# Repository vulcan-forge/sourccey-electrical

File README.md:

# Sourccey Electrical

Open-source hardware design files for the Sourccey electrical system.

This repository is intended to contain the complete KiCad design source,
component data, and documentation needed to inspect, modify, manufacture,
and assemble the hardware.

## Status

This repository contains the Sourccey v1.3.8 electrical design release.
Always review the release notes and complete your own manufacturing and safety
validation before building hardware.

## Repository layout

The repository is organized by editable design sources, manufacturing outputs,
and supporting documentation:

```text
.
├── pcb/
│   ├── <board-name>.kicad_pro
│   ├── <board-name>.kicad_sch
│   ├── <board-name>.kicad_pcb
│   ├── symbols/             # Project-specific KiCad symbols
│   └── footprints/          # Project-specific KiCad footprints
├── bom/
│   ├── bom.csv              # Human/reviewable bill of materials
│   └── pos.csv              # Pick-and-place / centroid data
├── fab/                     # Released Gerbers and drill files, if tracked
├── docs/                    # Design notes, assembly, and test instructions
└── README.md
```

The generic layout above describes the intended convention for additional
boards. The current checked-in release is organized as follows:

```text
.
|-- pcb/sourccey-v1.3.8/
|   |-- *.kicad_pro       # KiCad project
|   |-- *.kicad_sch       # Main and hierarchical schematics
|   |-- *.kicad_pcb       # PCB layout
|   |-- symbols/           # Project-specific KiCad symbols
|   |-- footprints/        # Project-specific KiCad footprints
|   `-- models/            # Optional 3D model references
|-- manufacturing/sourccey-v1.3.8/
|   |-- gerbers/           # Gerbers, drill files, and Gerber archive
|   |-- bom/               # Bill of materials exports
|   `-- cpl/               # Pick-and-place / component placement exports
|-- docs/                  # Design notes, assembly, and test instructions
`-- README.md
```

Each board should keep its `.kicad_pro`,
`.kicad_sch`, and `.kicad_pcb` files together. Do not commit KiCad lock files,
personal project settings, or backup files.

## Opening the design

The current design is Sourccey v1.3.8 and was saved with KiCad 9.0.

1. Install [KiCad 9](https://www.kicad.org/download/), including the standard
   symbol, footprint, and 3D-model libraries.
2. Clone this repository.
3. Open
   `pcb/sourccey-v1.3.8/sourccey_pcb.kicad_pro`.
4. Review the schematic before opening or editing the PCB.
5. Update the project libraries only with care: project-local symbols and
   footprints should be stored in this repository so the design remains
   reproducible.

The project includes its hierarchical `Power Electronics.kicad_sch` sheet and
the custom DRV8874 symbol and footprint. See the README under the version's
`models/` directory for two optional STEP models that are not yet included.

## BOM and POS data

The `manufacturing/sourccey-v1.3.8/` directory contains the files needed to
order and assemble the board:

- Gerbers for copper, solder mask, solder paste, silkscreen, and the board
  outline, plus the Gerber job file and packaged archive.
- PTH and NPTH drill files for plated and non-plated holes.
- A KiCad BOM export and a vendor-formatted BOM for purchasing.
- KiCad and vendor-formatted CPL (component placement / pick-and-place) data.

These are manufacturing outputs, not the editable source of truth. Regenerate
them from the released KiCad project whenever the design changes.

The BOM should identify at least:

- Reference designators
- Quantity
- Value and footprint
- Manufacturer and manufacturer part number, when known
- Distributor part number, when known
- Designator exclusions or DNP status

The POS file should identify each populated reference, X/Y position, rotation,
side, and the coordinate origin used for the export. BOM and POS exports are
manufacturing inputs: regenerate them from the released KiCad sources and
record the KiCad version and export settings in the release notes.

## Manufacturing components

Manufacturing outputs are generated from the released PCB source. A release
should include, or link to, the corresponding Gerber, drill, drawing, BOM, and
POS package. Keep generated outputs in `fab/` or a release artifact rather than
mixing them with editable KiCad source files.

The checked-in v1.3.8 outputs are under
`manufacturing/sourccey-v1.3.8/`, including original and vendor-formatted BOM
and CPL files, Gerbers, drill files, and the Gerber archive.

The PCB uses 2 oz copper on the copper layers. Confirm the fabricator's stackup
and copper-weight capabilities before ordering.

Before manufacturing, check at minimum:

- Schematic and PCB annotations are synchronized.
- Electrical rules and design rules pass.
- Board outline, mounting holes, clearances, and layer stack are correct.
- Footprints and 3D/component orientations are correct.
- BOM substitutions, DNP parts, polarity, and assembly side are reviewed.
- Gerbers and drill files are inspected in a separate viewer.

## Documentation

See the [Vulcan Robotics documentation](https://vulcanrobotics.ai/docs) for the
broader Sourccey project. This repository is the electrical reference for
wiring and board-level build details. The documentation site also links to the
related hardware, software, and LeRobot-compatible repositories. Software setup
and hardware-kit assembly instructions are currently listed there as coming
soon.

## Release notes

See [RELEASE_NOTES.md](RELEASE_NOTES.md) for the v1.3.8 release summary,
manufacturing package details, and validation record.

## Contributing

Please open an issue before making a substantial design change. Pull requests
should explain the motivation, identify affected boards, and include updated
schematic/PCB files and regenerated BOM/POS or manufacturing outputs when
applicable. Include screenshots or test results for changes that affect layout,
assembly, or electrical behavior.

## Licensing

Unless stated otherwise in a subdirectory, this project is released under the
[CERN Open Hardware Licence Version 2 - Strongly Reciprocal
(CERN-OHL-S-2.0)](https://gitlab.com/ohwr/project/cernohl/-/wikis/uploads/819d71bea3458f71fba6cf4fb0f2de6b/cern_ohl_s_v2.txt).
This license permits personal, educational, commercial, and manufacturing use.
If you distribute a modified design or a product based on it, you must preserve
the notices, make the corresponding source available, and license the modified
covered source under CERN-OHL-S-2.0. Private modifications do not need to be
published unless they are distributed.

Add the full license text as `LICENSE` before publishing the repository.

Third-party symbols, footprints, models, and datasheets may have separate
licenses. Preserve their notices and verify redistribution rights before
committing them.

## Disclaimer

This hardware is provided without warranty. You are responsible for reviewing
the design, complying with applicable laws and safety requirements, and
validating any manufactured or modified hardware before use.

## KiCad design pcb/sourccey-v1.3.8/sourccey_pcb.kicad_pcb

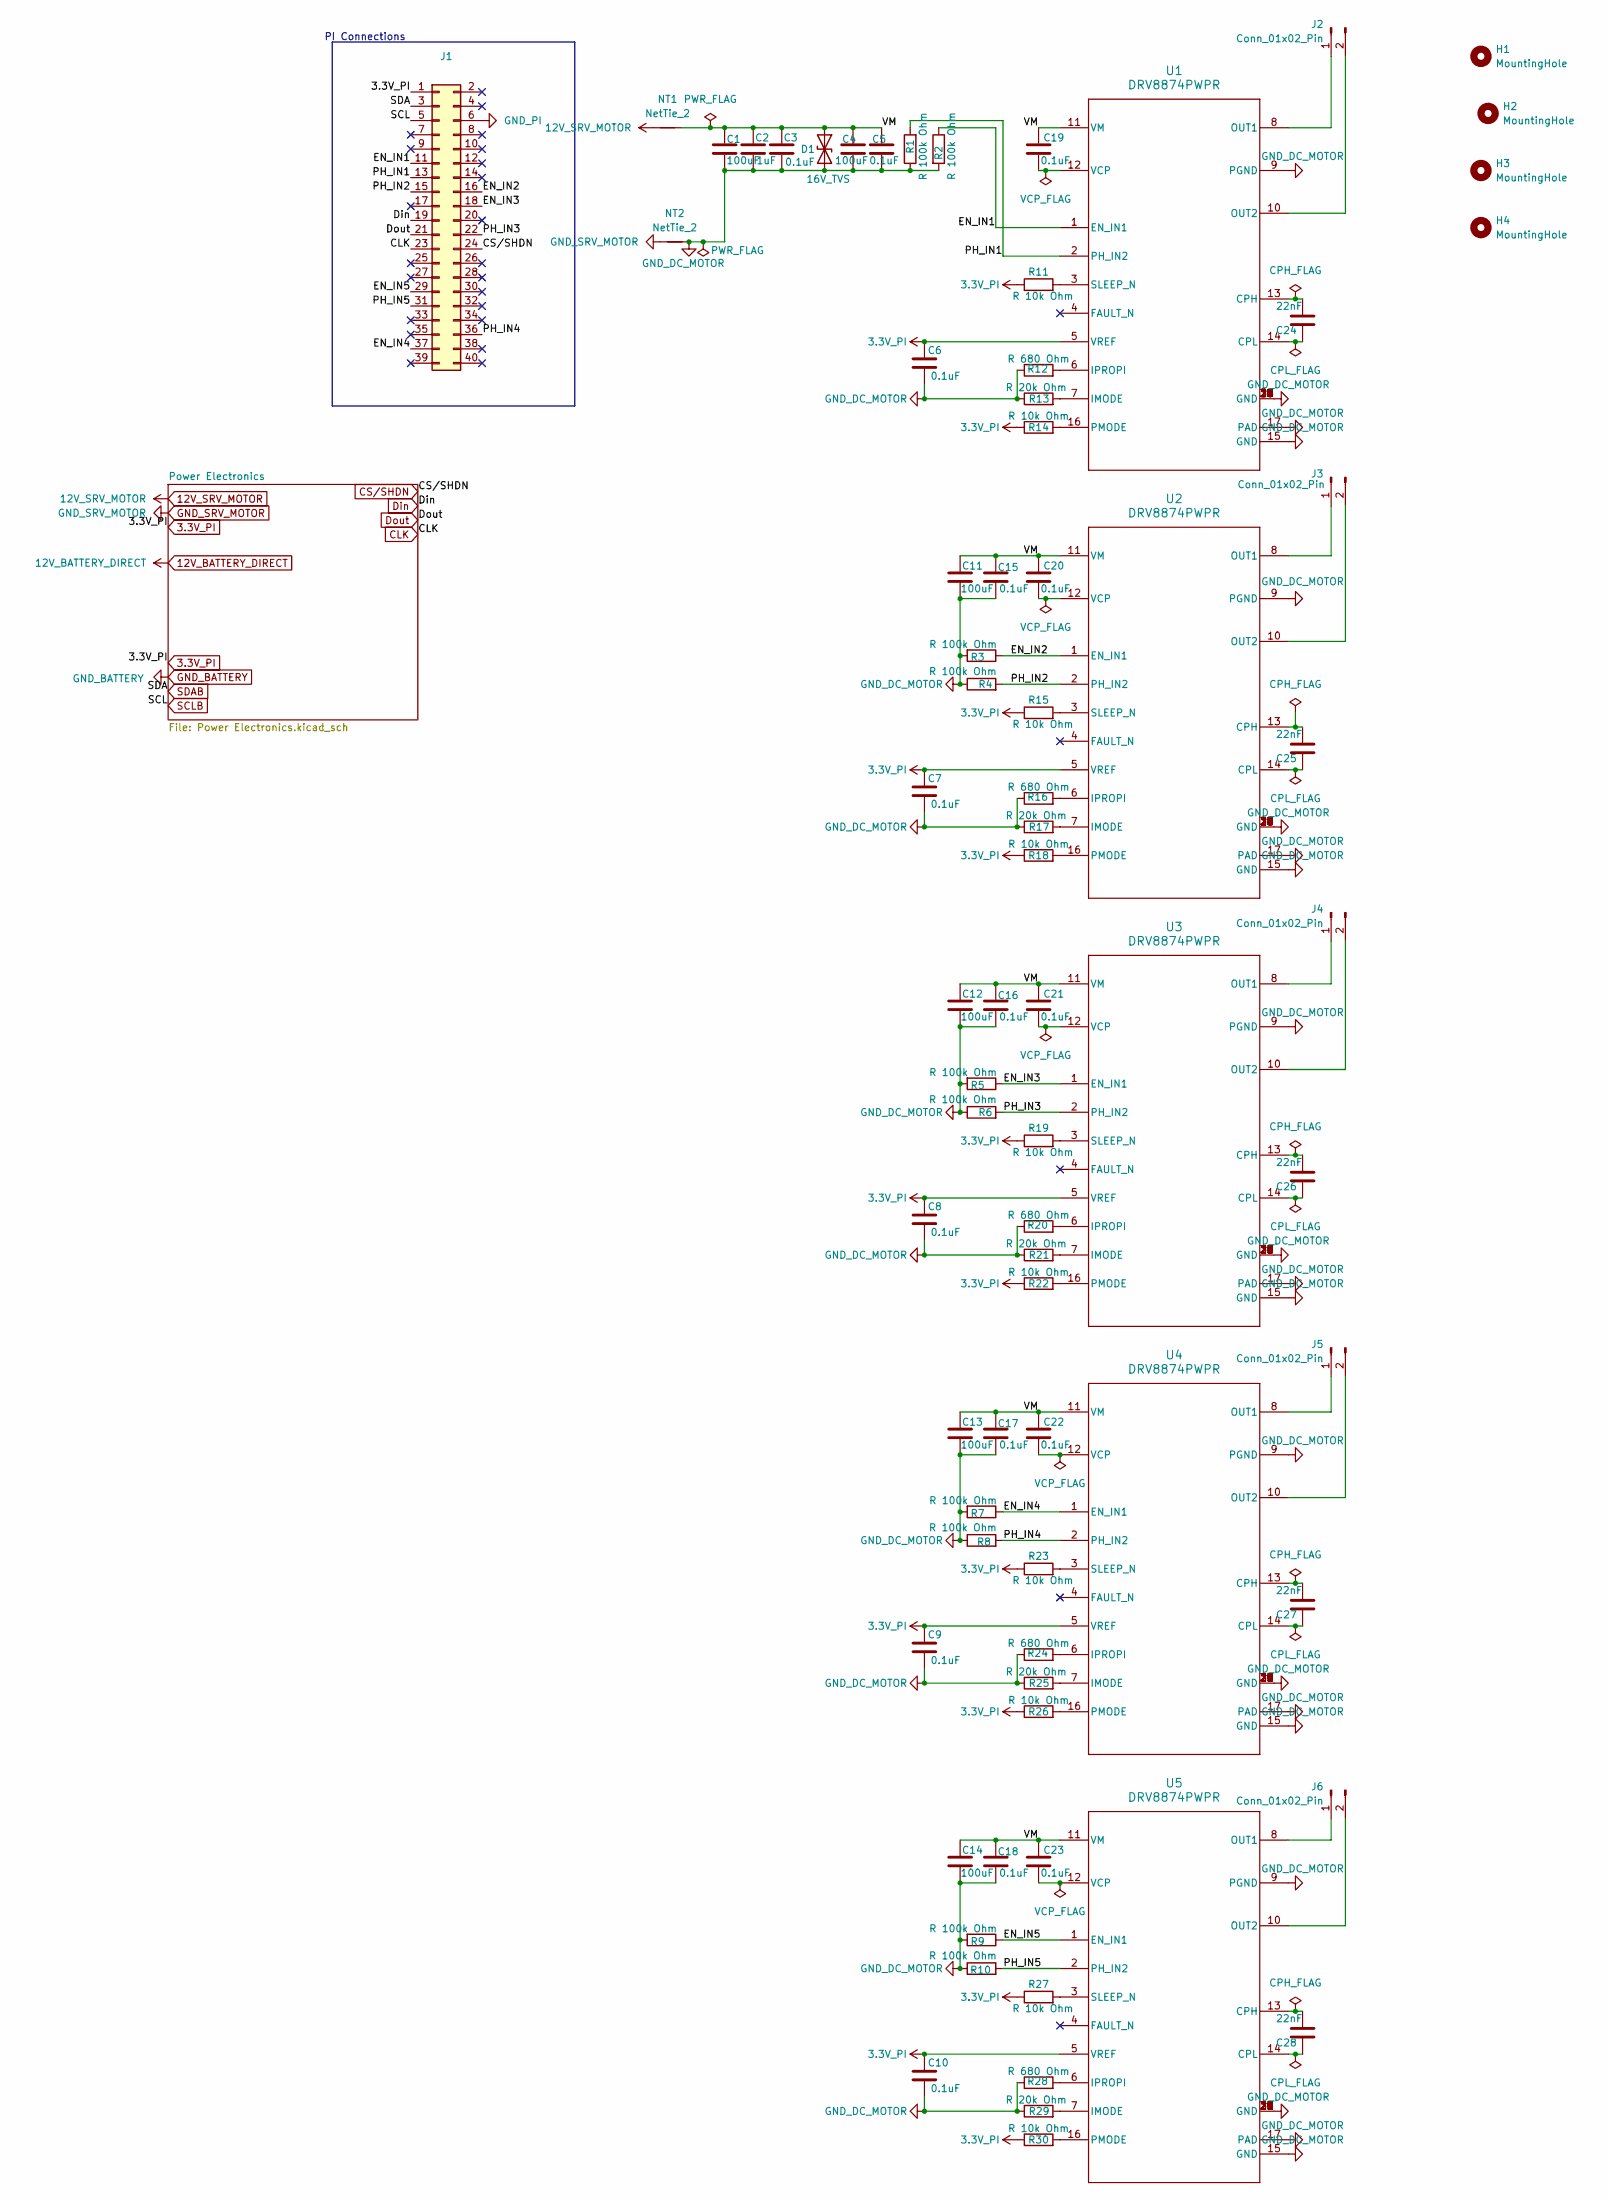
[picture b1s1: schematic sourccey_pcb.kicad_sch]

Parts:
C1, C4, C11, C12, C13, C14: 100uF; CP_Elec_6.3x7.7
C2: 1uF; C_0805_2012Metric
C3, C5, C6, C7, C8, C9, C10, C15, C16, C17, C18, C19, C20, C21, C22, C23: 0.1uF; C_0603_1608Metric
C24, C25, C26, C27, C28: 22nF; C_0402_1005Metric
D1: 16V_TVS; D_SMB
H1, H2, H3, H4: MountingHole; MountingHole_3.2mm_M3
J1: Conn_02x20_Odd_Even; PinHeader_2x20_P2.54mm_Vertical
J2, J3, J4, J5, J6: Conn_01x02_Pin; AMASS_XT30UPB-M_1x02_P5.0mm_Vertical
NT1, NT2: NetTie_2; NetTie-2_SMD_Pad2.0mm
R1, R2, R3, R4, R5, R6, R7, R8, R9, R10: R 100k Ohm; R_0805_2012Metric
R11, R14, R15, R18, R19, R22, R23, R26, R27, R30: R 10k Ohm; R_0805_2012Metric
R12, R16, R20, R24, R28: R 680 Ohm; R_0805_2012Metric
R13, R17, R21, R25, R29: R 20k Ohm; R_0805_2012Metric
U1, U2, U3, U4, U5: DRV8874PWPR; PWP0016J_L

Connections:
3.3V_PI: C6.2, C7.2, C8.2, C9.2, C10.2, J1.1, R11.1, R14.1, R15.1, R18.1, R19.1, R22.1, R23.1, R26.1, R27.1, R30.1, U1.5 (VREF), U2.5 (VREF), U3.5 (VREF), U4.5 (VREF), U5.5 (VREF); also elsewhere on the board
12V_SRV_MOTOR: NT1.1; also elsewhere on the board
/EN_IN1: J1.11, R2.1, U1.1 (EN_IN1)
/EN_IN2: J1.16, R3.1, U2.1 (EN_IN1)
/EN_IN3: J1.18, R5.1, U3.1 (EN_IN1)
/EN_IN4: J1.37, R7.1, U4.1 (EN_IN1)
/EN_IN5: J1.29, R9.1, U5.1 (EN_IN1)
/PH_IN1: J1.13, R1.2, U1.2 (PH_IN2)
/PH_IN2: J1.15, R4.2, U2.2 (PH_IN2)
/PH_IN3: J1.22, R6.2, U3.2 (PH_IN2)
/PH_IN4: J1.36, R8.2, U4.2 (PH_IN2)
/PH_IN5: J1.31, R10.2, U5.2 (PH_IN2)
/VM: C1.1, C2.1, C3.1, C4.1, C5.1, C11.1, C12.1, C13.1, C14.1, C15.1, C16.1, C17.1, C18.1, C19.1, C20.1, C21.1, C22.1, C23.1, D1.1 (A1), NT1.2, U1.11 (VM), U2.11 (VM), U3.11 (VM), U4.11 (VM), U5.11 (VM)
CLK: J1.23; also elsewhere on the board
CS/SHDN: J1.24; also elsewhere on the board
Din: J1.19; also elsewhere on the board
Dout: J1.21; also elsewhere on the board
GND_DC_MOTOR: C1.2, C2.2, C3.2, C4.2, C5.2, C6.1, C7.1, C8.1, C9.1, C10.1, C11.2, C12.2, C13.2, C14.2, C15.2, C16.2, C17.2, C18.2, D1.2 (A2), NT2.2, R1.1, R2.2, R3.2, R4.1, R5.2, R6.1, R7.2, R8.1, R9.2, R10.1, R12.1, R13.1, R16.1, R17.1, R20.1, R21.1, R24.1, R25.1, R28.1, R29.1, U1.9 (PGND), U1.15 (GND), U1.17 (PAD), U1.18 (GND), U1.19 (GND), U1.20 (GND), U1.21 (GND), U1.22 (GND), U1.23 (GND), U1.24 (GND), U1.25 (GND), U1.26 (GND), U1.27 (GND), U1.28 (GND), U1.29 (GND), U1.30 (GND), U1.31 (GND), U1.32 (GND), U2.9 (PGND), U2.15 (GND), U2.17 (PAD), U2.18 (GND), U2.19 (GND), U2.20 (GND), U2.21 (GND), U2.22 (GND), U2.23 (GND), U2.24 (GND), U2.25 (GND), U2.26 (GND), U2.27 (GND), U2.28 (GND), U2.29 (GND), U2.30 (GND), U2.31 (GND), U2.32 (GND), U3.9 (PGND), U3.15 (GND), U3.17 (PAD), U3.18 (GND), U3.19 (GND), U3.20 (GND), U3.21 (GND), U3.22 (GND), U3.23 (GND), U3.24 (GND), U3.25 (GND), U3.26 (GND), U3.27 (GND), U3.28 (GND), U3.29 (GND), U3.30 (GND), U3.31 (GND), U3.32 (GND), U4.9 (PGND), U4.15 (GND), U4.17 (PAD), U4.18 (GND), U4.19 (GND), U4.20 (GND), U4.21 (GND), U4.22 (GND), U4.23 (GND), U4.24 (GND), U4.25 (GND), U4.26 (GND), U4.27 (GND), U4.28 (GND), U4.29 (GND), U4.30 (GND), U4.31 (GND), U4.32 (GND), U5.9 (PGND), U5.15 (GND), U5.17 (PAD), U5.18 (GND), U5.19 (GND), U5.20 (GND), U5.21 (GND), U5.22 (GND), U5.23 (GND), U5.24 (GND), U5.25 (GND), U5.26 (GND), U5.27 (GND), U5.28 (GND), U5.29 (GND), U5.30 (GND), U5.31 (GND), U5.32 (GND); also elsewhere on the board
GND_PI: J1.6; also elsewhere on the board
GND_SRV_MOTOR: NT2.1; also elsewhere on the board
unnamed: J2.1, U1.8 (OUT1)
unnamed: J2.2, U1.10 (OUT2)
unnamed: J3.1, U2.8 (OUT1)
unnamed: J3.2, U2.10 (OUT2)
unnamed: J4.1, U3.8 (OUT1)
unnamed: J4.2, U3.10 (OUT2)
unnamed: J5.1, U4.8 (OUT1)
unnamed: J5.2, U4.10 (OUT2)
unnamed: J6.1, U5.8 (OUT1)
unnamed: J6.2, U5.10 (OUT2)
unnamed: C24.1, U1.13 (CPH)
unnamed: C24.2, U1.14 (CPL)
unnamed: R13.2, U1.7 (IMODE)
unnamed: R12.2, U1.6 (IPROPI)
unnamed: R14.2, U1.16 (PMODE)
unnamed: R11.2, U1.3 (SLEEP_N)
unnamed: C19.2, U1.12 (VCP)
unnamed: C25.1, U2.13 (CPH)
unnamed: C25.2, U2.14 (CPL)
unnamed: R17.2, U2.7 (IMODE)
unnamed: R16.2, U2.6 (IPROPI)
unnamed: R18.2, U2.16 (PMODE)
unnamed: R15.2, U2.3 (SLEEP_N)
unnamed: C20.2, U2.12 (VCP)
unnamed: C26.1, U3.13 (CPH)
unnamed: C26.2, U3.14 (CPL)
unnamed: R21.2, U3.7 (IMODE)
unnamed: R20.2, U3.6 (IPROPI)
unnamed: R22.2, U3.16 (PMODE)
unnamed: R19.2, U3.3 (SLEEP_N)
unnamed: C21.2, U3.12 (VCP)
unnamed: C27.1, U4.13 (CPH)
unnamed: C27.2, U4.14 (CPL)
unnamed: R25.2, U4.7 (IMODE)
unnamed: R24.2, U4.6 (IPROPI)
unnamed: R26.2, U4.16 (PMODE)
unnamed: R23.2, U4.3 (SLEEP_N)
unnamed: C22.2, U4.12 (VCP)
unnamed: C28.1, U5.13 (CPH)
unnamed: C28.2, U5.14 (CPL)
unnamed: R29.2, U5.7 (IMODE)
unnamed: R28.2, U5.6 (IPROPI)
unnamed: R30.2, U5.16 (PMODE)
unnamed: R27.2, U5.3 (SLEEP_N)
unnamed: C23.2, U5.12 (VCP)
SCLB: J1.5; also elsewhere on the board
SDAB: J1.3; also elsewhere on the board

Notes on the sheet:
PI Connections

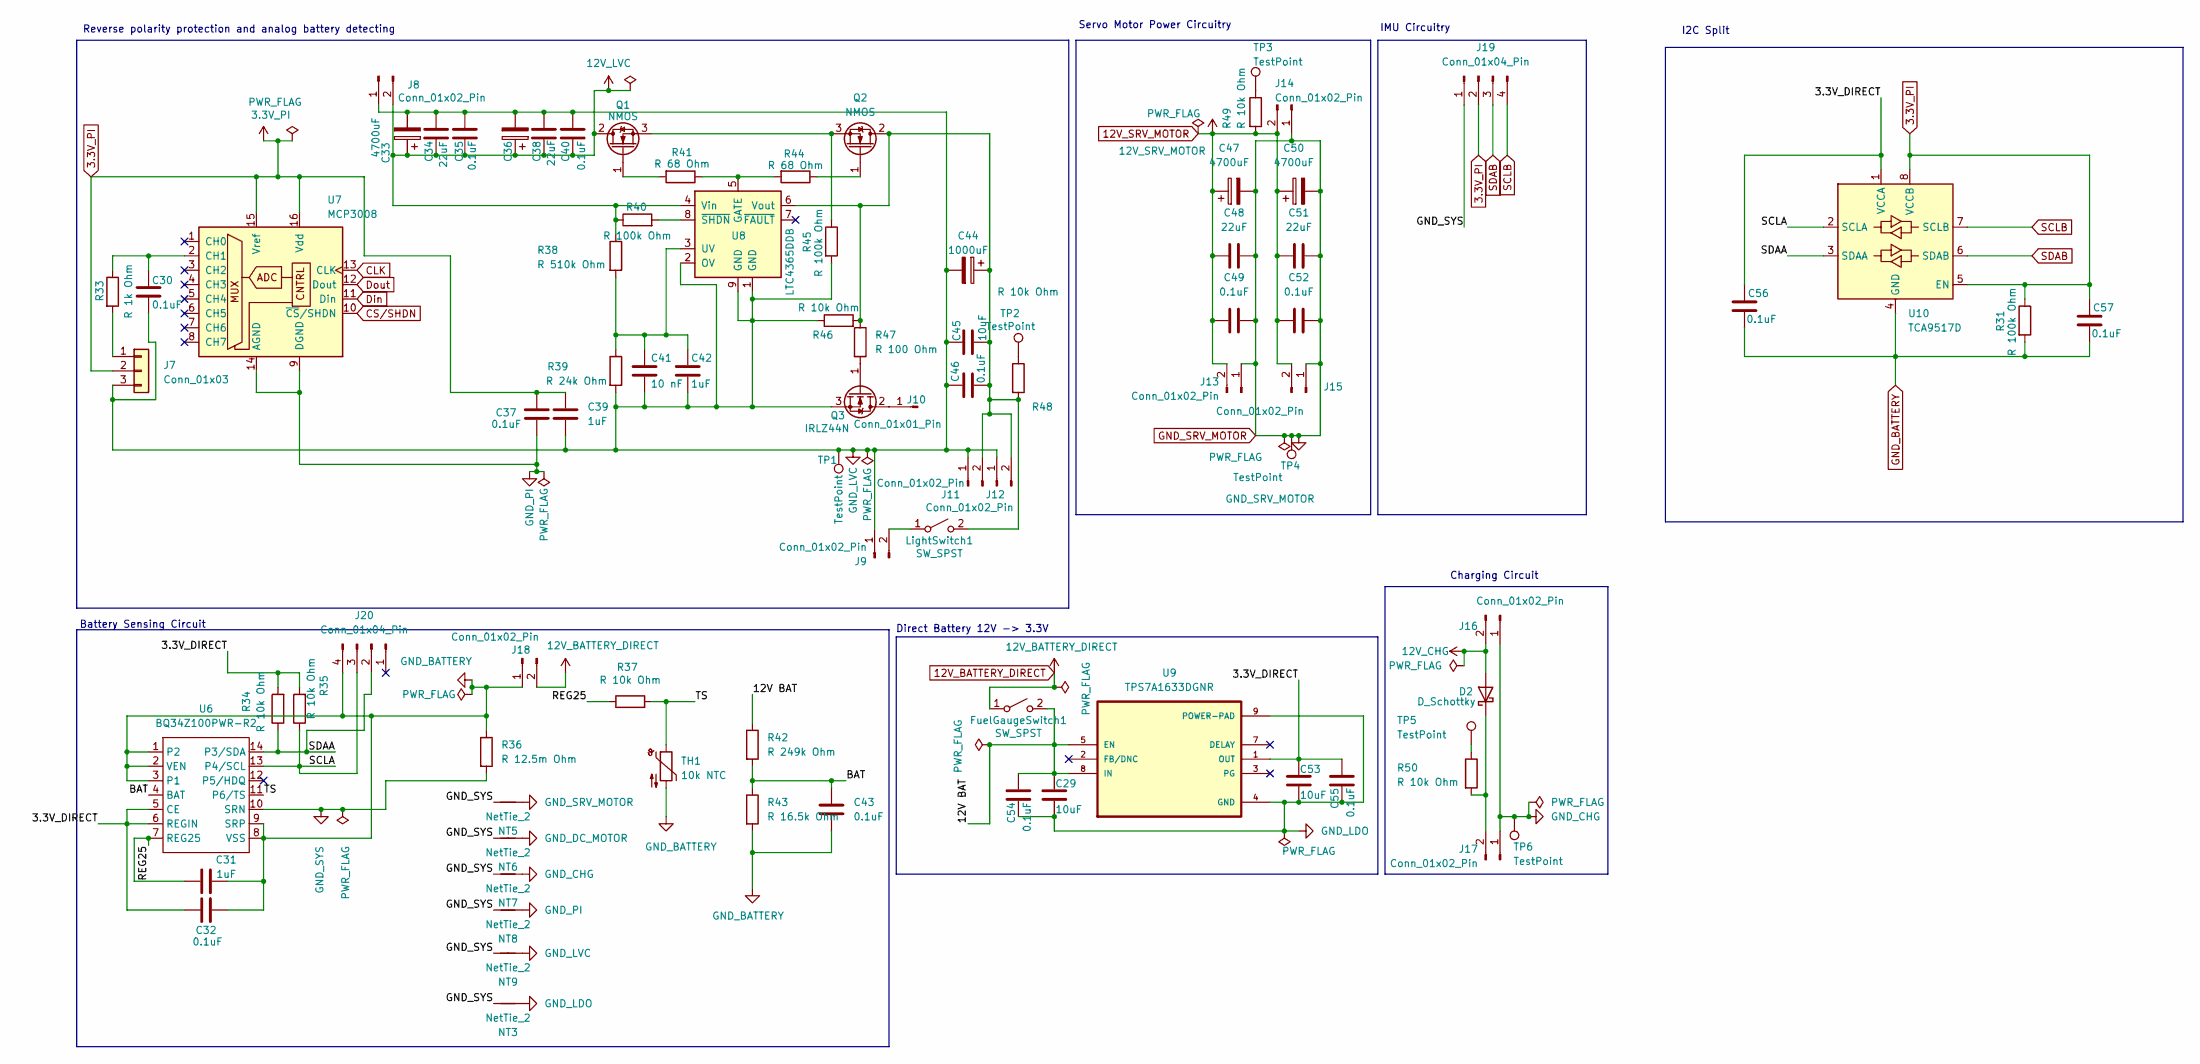
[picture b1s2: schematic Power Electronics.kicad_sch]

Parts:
C29, C45, C53: 10uF; C_0805_2012Metric
C30, C32, C35, C37, C40, C43, C46, C49, C52, C54, C55, C56, C57: 0.1uF; C_0603_1608Metric
C31, C39, C42: 1uF; C_0805_2012Metric
C33, C36, C47, C50: 4700uF; CP_Radial_D13.0mm_P5.00mm
C34, C38, C48, C51: 22uF; C_1206_3216Metric
C41: 10 nF; C_0603_1608Metric
C44: 1000uF; CP_Radial_D10.0mm_P5.00mm
D2: D_Schottky; D_SMB
FuelGaugeSwitch1: SW_SPST; SW_SPDT_PCM12
J7: Conn_01x03; JST_XH_B3B-XH-A_1x03_P2.50mm_Vertical
J8, J9, J11, J12, J13, J14, J15, J16, J17, J18: Conn_01x02_Pin; AMASS_XT30UPB-M_1x02_P5.0mm_Vertical
J10: Conn_01x01_Pin; PinHeader_1x01_P2.54mm_Vertical
J19: Conn_01x04_Pin; JST_SH_BM04B-SRSS-TB_1x04-1MP_P1.00mm_Vertical
J20: Conn_01x04_Pin; Molex_KK-254_AE-6410-04A_1x04_P2.54mm_Vertical
LightSwitch1: SW_SPST; SW_SPDT_PCM12
NT3, NT5, NT6, NT7, NT8, NT9: NetTie_2; NetTie-2_SMD_Pad2.0mm
Q1, Q2: NMOS; TO-220-3_Vertical
Q3: IRLZ44N; TO-220-3_Vertical
R31, R40, R45: R 100k Ohm; R_0805_2012Metric
R33: R 1k Ohm; R_0805_2012Metric
R34, R35, R37, R46, R48, R49, R50: R 10k Ohm; R_0805_2012Metric
R36: R 12.5m Ohm; R_2512_6332Metric
R38: R 510k Ohm; R_0805_2012Metric
R39: R 24k Ohm; R_0805_2012Metric
R41, R44: R 68 Ohm; R_0603_1608Metric
R42: R 249k Ohm; R_0805_2012Metric
R43: R 16.5k Ohm; R_0805_2012Metric
R47: R 100 Ohm; R_0805_2012Metric
TH1: 10k NTC; JST_XH_B2B-XH-A_1x02_P2.50mm_Vertical
TP1, TP2, TP3, TP4, TP5, TP6: TestPoint; TestPoint_Pad_2.0x2.0mm
U6: BQ34Z100PWR-R2; TSSOP-14_4.4x5mm_P0.65mm
U7: MCP3008; SOIC-16_3.9x9.9mm_P1.27mm
U8: LTC4365DDB; DFN-8-1EP_2x3mm_P0.5mm_EP0.61x2.2mm
U9: TPS7A1633DGNR; MSOP-8-1EP_3x3mm_P0.65mm_EP1.5x1.8mm
U10: TCA9517D; SOIC-8_3.9x4.9mm_P1.27mm

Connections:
3.3V_PI: C37.2, C39.1, C57.2, J7.2, J19.2, R31.1, U7.15 (Vref), U7.16 (Vdd), U10.5 (EN), U10.8 (VCCB); also elsewhere on the board
12V_BATTERY_DIRECT: FuelGaugeSwitch1.1 (A), J18.2
12V_CHG: D2.2 (A), J16.2
12V_LVC: C33.1, C34.2, C35.1, C36.1, C38.1, C40.1, J8.2, Q1.2 (D), R38.1, R40.1, U8.4 (Vin)
12V_SRV_MOTOR: C47.1, C48.2, C49.1, C50.1, C51.2, C52.2, J13.2, J14.2, J15.2, R49.2; also elsewhere on the board
/Power Electronics/3.3V_DIRECT: C32.1, C53.1, C55.2, C56.2, R34.2, R35.2, U6.5 (CE), U6.6 (REGIN), U9.1 (OUT), U10.1 (VCCA)
/Power Electronics/12V BAT: C29.1, C54.2, FuelGaugeSwitch1.2 (B), R42.1, U9.5 (EN), U9.8 (IN)
/Power Electronics/BAT: C43.1, R42.2, R43.1, U6.4 (BAT)
/Power Electronics/REG25: C31.1, R37.1, U6.7 (REG25)
/Power Electronics/SCLA: J20.3, R35.1, U6.13 (P4/SCL), U10.2 (SCLA)
/Power Electronics/SDAA: J20.2, R34.1, U6.14 (P3/SDA), U10.3 (SDAA)
/Power Electronics/TS: R37.2, TH1.1, U6.11 (P6/TS)
CLK: U7.13 (CLK); also elsewhere on the board
CS/SHDN: U7.10 (~CS/SHDN); also elsewhere on the board
Din: U7.11 (Din); also elsewhere on the board
Dout: U7.12 (Dout); also elsewhere on the board
GND_BATTERY: C31.2, C32.2, C43.2, C56.1, C57.1, J18.1, J20.4, R31.2, R36.1, R43.2, TH1.2, U6.1 (P2), U6.2 (VEN), U6.3 (P1), U6.8 (VSS), U6.9 (SRP), U10.4 (GND)
GND_CHG: J16.1, J17.1, NT7.1, TP6.1
GND_DC_MOTOR: NT6.1; also elsewhere on the board
GND_LDO: C29.2, C53.2, C54.1, C55.1, NT3.1, U9.4 (GND), U9.9 (POWER-PAD)
GND_LVC: C30.1, C33.2, C34.1, C35.2, C36.2, C38.2, C39.2, C40.2, C41.1, C42.2, C44.2, C45.1, C46.2, J7.3, J8.1, J9.1, J11.1, J12.1, NT9.1, Q3.3 (S), R39.2, R45.2, R46.1, TP1.1, U8.1 (GND), U8.2 (OV), U8.9 (GND)
GND_PI: C37.1, NT8.1, U7.9 (DGND), U7.14 (AGND); also elsewhere on the board
GND_SRV_MOTOR: C47.2, C48.1, C49.2, C50.2, C51.1, C52.1, J13.1, J14.1, J15.1, NT5.1, TP4.1; also elsewhere on the board
GND_SYS: J19.1, NT3.2, NT5.2, NT6.2, NT7.2, NT8.2, NT9.2, R36.2, U6.10 (SRN)
unnamed: D2.1 (K), J17.2, R50.2
unnamed: J7.1, R33.2
unnamed: J9.2, LightSwitch1.1 (A)
unnamed: J10.1, Q3.2 (D)
unnamed: C44.1, C45.2, C46.1, J11.2, J12.2, LightSwitch1.2 (B), Q2.2 (D), R46.2, R47.1, R48.2, U8.6 (Vout)
unnamed: Q1.1 (G), R41.2
unnamed: Q1.3 (S), Q2.3 (S), R45.1
unnamed: Q2.1 (G), R44.1
unnamed: Q3.1 (G), R47.2
unnamed: R48.1, TP2.1
unnamed: R49.1, TP3.1
unnamed: R50.1, TP5.1
unnamed: C30.2, R33.1, U7.2 (CH1)
unnamed: R41.1, R44.2, U8.5 (GATE)
unnamed: C41.2, C42.1, R38.2, R39.1, U8.3 (UV)
unnamed: R40.2, U8.8 (~SHDN)
SCLB: J19.4, U10.7 (SCLB); also elsewhere on the board
SDAB: J19.3, U10.6 (SDAB); also elsewhere on the board

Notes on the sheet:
Reverse polarity protection and analog battery detecting
I2C Split
Servo Motor Power Circuitry
IMU Circuitry
Battery Sensing Circuit
Charging Circuit
Direct Battery 12V -> 3.3V

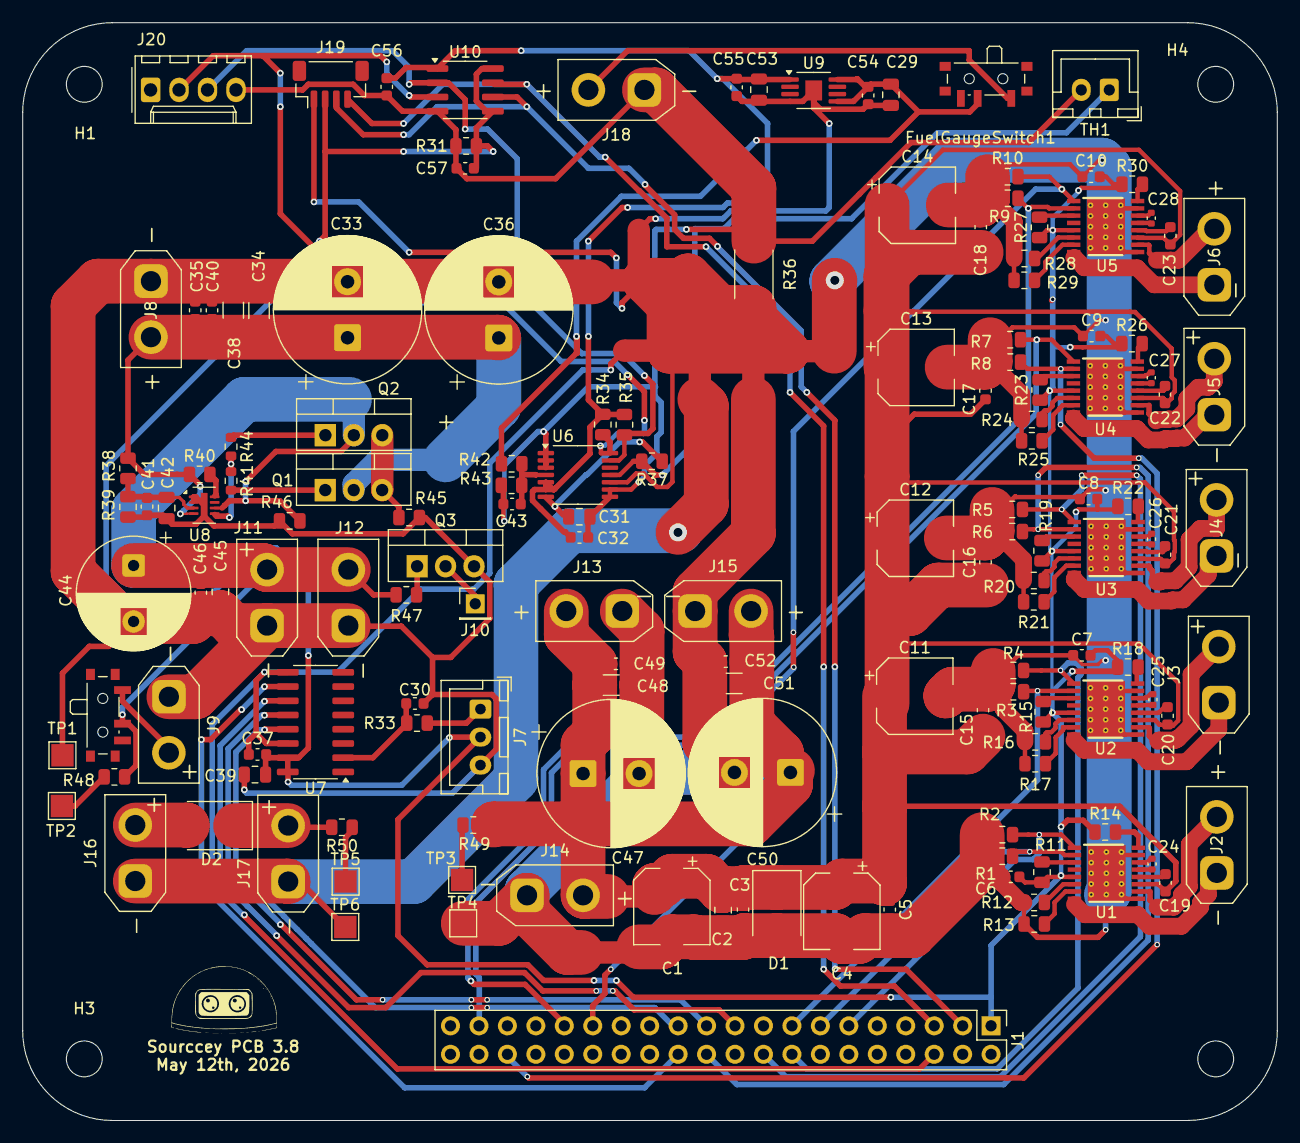
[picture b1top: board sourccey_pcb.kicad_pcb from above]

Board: 2 copper layers, 112.0 x 98.0 mm, 162 parts (0 on the bottom side), 98 nets.
